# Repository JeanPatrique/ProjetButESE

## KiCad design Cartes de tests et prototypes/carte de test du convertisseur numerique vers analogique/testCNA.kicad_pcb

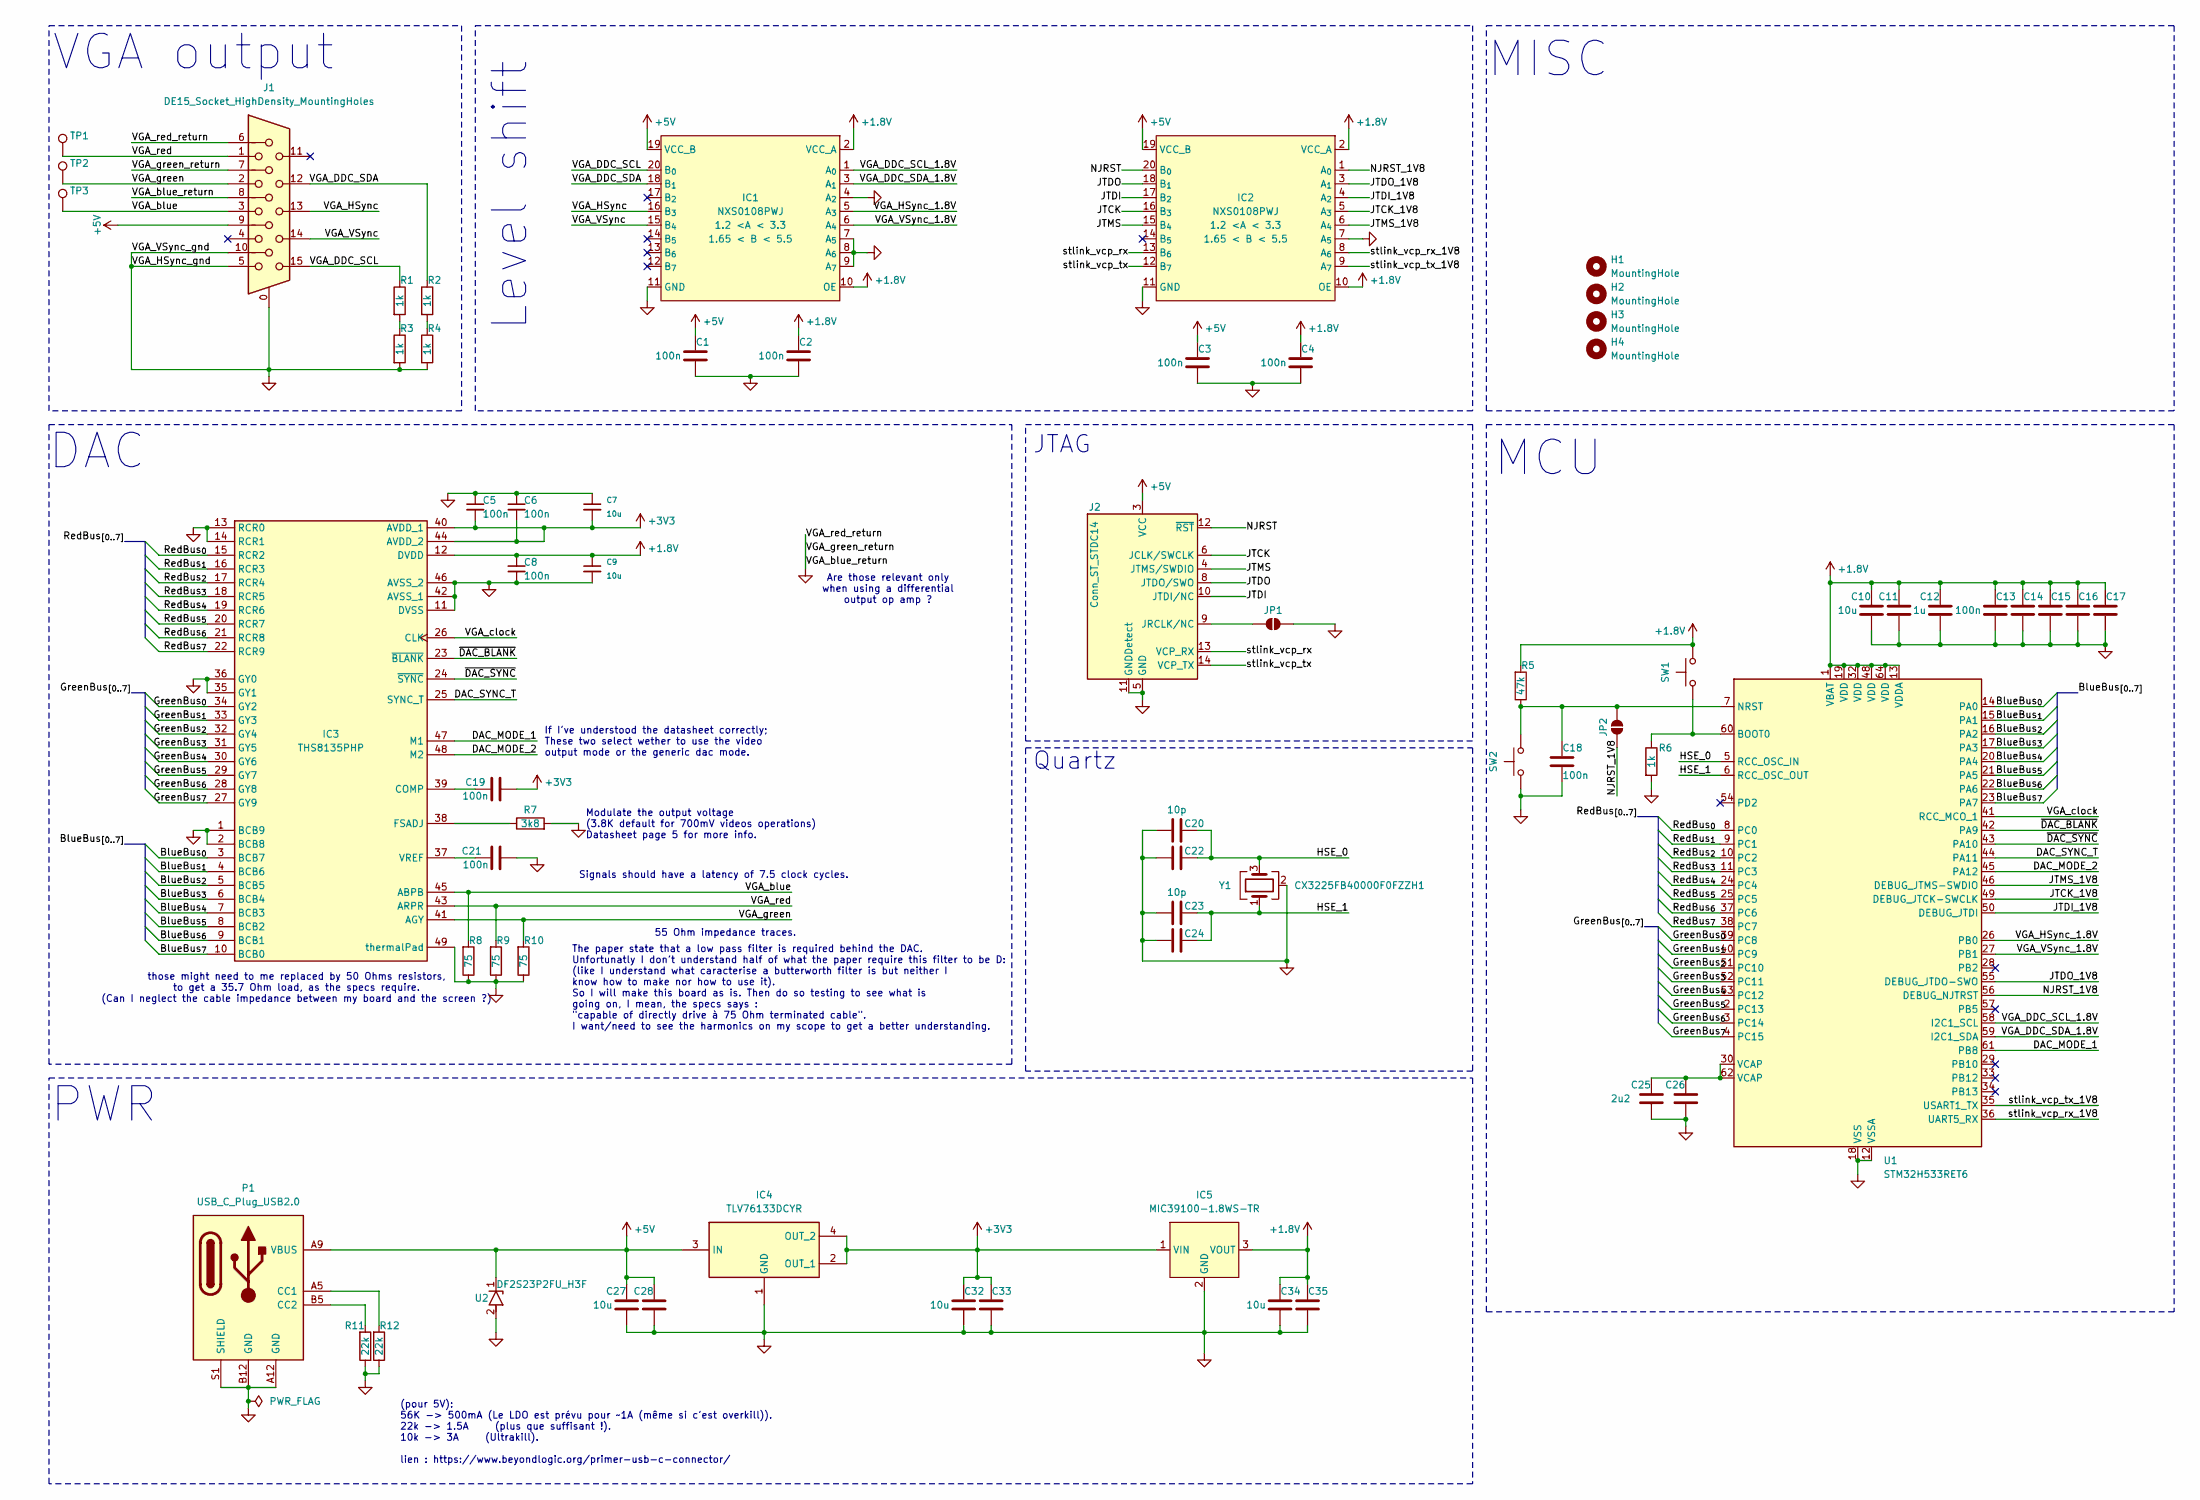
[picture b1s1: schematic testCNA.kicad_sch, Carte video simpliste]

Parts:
C1, C2, C3, C4, C5, C6, C8, C13, C14, C15, C16, C17, C18, C19, C21: 100n; C_0805_2012Metric_Pad1.18x1.45mm_HandSolder; Mouser Part Number 581-08055C104ZAT2A
C7, C9, C10, C11, C27, C28, C32, C33, C34, C35: 10u; C_1206_3216Metric_Pad1.33x1.80mm_HandSolder; Mouser Part Number 603-CC126ZKY5V7BB106
C12: 1u; C_1206_3216Metric_Pad1.33x1.80mm_HandSolder; Mouser Part Number 810-C3216X7R1H105K
C20, C22, C23, C24: 10p; C_1206_3216Metric_Pad1.33x1.80mm_HandSolder; Mouser Part Number 80-C1206C100J5GACTU
C25, C26: 2u2; C_1206_3216Metric_Pad1.33x1.80mm_HandSolder; Mouser Part Number 603-CC126KKX7R6BB225
H1, H2, H3, H4: MountingHole; MountingHole_3.2mm_M3
IC1, IC2: NXS0108PWJ; TSSOP-20_4.4x6.5mm_P0.65mm; Mouser Part Number 771-NXS0108PWJ
IC3: THS8135PHP; Texas_PHP0048E_HTQFP-48-1EP_7x7mm_P0.5mm_EP6.5x6.5mm_Mask3.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; Mouser Part Number 595-THS8135PHP
IC4: TLV76133DCYR; SOT-223; Mouser Part Number 595-TLV76133DCYR
IC5: MIC39100-1.8WS-TR; SOT-223-3_TabPin2; Mouser Part Number 998-MIC39100-1.8WSTR
J1: DE15_Socket_HighDensity_MountingHoles; DSUB-15_Socket_Horizontal_P2.77x2.84mm_EdgePinOffset7.70mm_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
J2: Conn_ST_STDC14; PinHeader_2x07_P1.27mm_Vertical_SMD
JP1, JP2: SolderJumper_2_Open; SolderJumper-2_P1.3mm_Open_RoundedPad1.0x1.5mm
P1: USB_C_Plug_USB2.0; USB_C_Receptacle_GCT_USB4125-xx-x-0190_6P_TopMnt_Horizontal; Mouser Part Number 179-UJCHGSMT2P6TR
R1, R2, R3, R4, R6: 1k; R_1206_3216Metric_Pad1.30x1.75mm_HandSolder; Mouser Part Number 603-RT1206DRD071KL
R5: 47k; R_1206_3216Metric_Pad1.30x1.75mm_HandSolder; Mouser Part Number 603-RT1206FRD0747KL
R7: 3k8; R_1206_3216Metric_Pad1.30x1.75mm_HandSolder; Mouser Part Number 603-RT1206BRD073K83L
R8, R9, R10: 75; R_1206_3216Metric_Pad1.30x1.75mm_HandSolder; Mouser Part Number 667-ERA-8AEB750V
R11, R12: 22k; R_1206_3216Metric_Pad1.30x1.75mm_HandSolder; Mouser Part Number 603-RT1206FRD0722KL
SW1, SW2: TS02-66-100-BK-100-SCR-D; SW_PUSH_6mm_H4.3mm; Mouser Part Number 179-TS0266100BK100SC
TP1, TP2, TP3: TestPoint; TestPoint_THTPad_D2.0mm_Drill1.0mm
U1: STM32H533RET6; LQFP-64_10x10mm_P0.5mm; Mouser Part Number 511-STM32H533RET6
U2: DF2S23P2FU_H3F; D_SOD-323_HandSoldering; Mouser Part Number 757-DF2S23P2FUH3F
Y1: CX3225FB40000F0FZZH1; Crystal_SMD_3225-4Pin_3.2x2.5mm_HandSoldering; Mouser Part Number 581-CX3225FB40F0FZZH

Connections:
+1.8V: C2.1, C4.1, C8.1, C9.1, C10.1, C11.1, C12.1, C13.1, C14.1, C15.1, C16.1, C17.1, C34.1, C35.1, IC1.2 (VCC_A), IC1.10 (OE), IC2.2 (VCC_A), IC2.10 (OE), IC3.12 (DVDD), IC5.3 (VOUT), R5.1, SW1.2, U1.1 (VBAT), U1.13 (VDDA), U1.19 (VDD), U1.32 (VDD), U1.48 (VDD), U1.64 (VDD)
+3V3: C5.2, C6.2, C7.2, C19.2, C32.1, C33.1, IC3.40 (AVDD_1), IC3.44 (AVDD_2), IC4.2 (OUT_1), IC4.4 (OUT_2), IC5.1 (VIN)
+5V: C1.1, C3.1, C27.1, C28.1, IC1.19 (VCC_B), IC2.19 (VCC_B), IC4.3 (IN), J1.9, J2.3 (VCC), P1.A9 (VBUS), P1.B9 (VBUS), U2.1
/BlueBus_{0}: IC3.3 (BCB7), U1.14 (PA0)
/BlueBus_{1}: IC3.4 (BCB6), U1.15 (PA1)
/BlueBus_{2}: IC3.5 (BCB5), U1.16 (PA2)
/BlueBus_{3}: IC3.6 (BCB4), U1.17 (PA3)
/BlueBus_{4}: IC3.7 (BCB3), U1.20 (PA4)
/BlueBus_{5}: IC3.8 (BCB2), U1.21 (PA5)
/BlueBus_{6}: IC3.9 (BCB1), U1.22 (PA6)
/BlueBus_{7}: IC3.10 (BCB0), U1.23 (PA7)
/DAC_MODE_1: IC3.47 (M1), U1.61 (PB8)
/DAC_MODE_2: IC3.48 (M2), U1.45 (PA12)
/DAC_SYNC_T: IC3.25 (SYNC_T), U1.44 (PA11)
/GreenBus_{0}: IC3.34 (GY2), U1.39 (PC8)
/GreenBus_{1}: IC3.33 (GY3), U1.40 (PC9)
/GreenBus_{2}: IC3.32 (GY4), U1.51 (PC10)
/GreenBus_{3}: IC3.31 (GY5), U1.52 (PC11)
/GreenBus_{4}: IC3.30 (GY6), U1.53 (PC12)
/GreenBus_{5}: IC3.29 (GY7), U1.2 (PC13)
/GreenBus_{6}: IC3.28 (GY8), U1.3 (PC14)
/GreenBus_{7}: IC3.27 (GY9), U1.4 (PC15)
/HSE_0: C20.2, C22.2, U1.5 (RCC_OSC_IN), Y1.3
/HSE_1: C23.2, C24.2, U1.6 (RCC_OSC_OUT), Y1.1
/JTCK: IC2.16 (B_{3}), J2.6 (JCLK/SWCLK)
/JTCK_1V8: IC2.5 (A_{3}), U1.49 (DEBUG_JTCK-SWCLK)
/JTDI: IC2.17 (B_{2}), J2.10 (JTDI/NC)
/JTDI_1V8: IC2.4 (A_{2}), U1.50 (DEBUG_JTDI)
/JTDO: IC2.18 (B_{1}), J2.8 (JTDO/SWO)
/JTDO_1V8: IC2.3 (A_{1}), U1.55 (DEBUG_JTDO-SWO)
/JTMS: IC2.15 (B_{4}), J2.4 (JTMS/SWDIO)
/JTMS_1V8: IC2.6 (A_{4}), U1.46 (DEBUG_JTMS-SWDIO)
/NJRST: IC2.20 (B_{0}), J2.12 (~RST)
/NJRST_1V8: IC2.1 (A_{0}), JP2.1 (A), U1.56 (DEBUG_NJTRST)
/RedBus_{0}: IC3.15 (RCR2), U1.8 (PC0)
/RedBus_{1}: IC3.16 (RCR3), U1.9 (PC1)
/RedBus_{2}: IC3.17 (RCR4), U1.10 (PC2)
/RedBus_{3}: IC3.18 (RCR5), U1.11 (PC3)
/RedBus_{4}: IC3.19 (RCR6), U1.24 (PC4)
/RedBus_{5}: IC3.20 (RCR7), U1.25 (PC5)
/RedBus_{6}: IC3.21 (RCR8), U1.37 (PC6)
/RedBus_{7}: IC3.22 (RCR9), U1.38 (PC7)
/VGA_DDC_SCL: IC1.20 (B_{0}), J1.15, R1.1
/VGA_DDC_SCL_1.8V: IC1.1 (A_{0}), U1.58 (I2C1_SCL)
/VGA_DDC_SDA: IC1.18 (B_{1}), J1.12, R2.1
/VGA_DDC_SDA_1.8V: IC1.3 (A_{1}), U1.59 (I2C1_SDA)
/VGA_HSync: IC1.16 (B_{3}), J1.13
/VGA_HSync_1.8V: IC1.5 (A_{3}), U1.26 (PB0)
/VGA_VSync: IC1.15 (B_{4}), J1.14
/VGA_VSync_1.8V: IC1.6 (A_{4}), U1.27 (PB1)
/VGA_blue: IC3.45 (ABPB), J1.3, R8.1, TP3.1
/VGA_clock: IC3.26 (CLK), U1.41 (RCC_MCO_1)
/VGA_green: IC3.41 (AGY), J1.2, R10.1, TP2.1
/VGA_red: IC3.43 (ARPR), J1.1, R9.1, TP1.1
/stlink_vcp_rx: IC2.13 (B_{6}), J2.13 (VCP_RX)
/stlink_vcp_rx_1V8: IC2.8 (A_{6}), U1.36 (UART5_RX)
/stlink_vcp_tx: IC2.12 (B_{7}), J2.14 (VCP_TX)
/stlink_vcp_tx_1V8: IC2.9 (A_{7}), U1.35 (USART1_TX)
/~DAC_BLANK: IC3.23 (~BLANK), U1.42 (PA9)
/~DAC_SYNC: IC3.24 (~SYNC), U1.43 (PA10)
GND: C1.2, C2.2, C3.2, C4.2, C5.1, C6.1, C7.1, C8.2, C9.2, C10.2, C11.2, C12.2, C13.2, C14.2, C15.2, C16.2, C17.2, C18.2, C20.1, C21.2, C22.1, C23.1, C24.1, C25.2, C26.2, C27.2, C28.2, C32.2, C33.2, C34.2, C35.2, IC1.4 (A_{2}), IC1.7 (A_{5}), IC1.8 (A_{6}), IC1.9 (A_{7}), IC1.11 (GND), IC2.7 (A_{5}), IC2.11 (GND), IC3.1 (BCB9), IC3.2 (BCB8), IC3.11 (DVSS), IC3.13 (RCR0), IC3.14 (RCR1), IC3.35 (GY1), IC3.36 (GY0), IC3.42 (AVSS_1), IC3.46 (AVSS_2), IC3.49 (thermalPad), IC4.1 (GND), IC5.2 (GND), J1.0, J1.5, J1.6, J1.7, J1.8, J1.10, J2.5 (GND), J2.7 (GND), J2.11 (GNDDetect), JP1.2 (B), P1.A12 (GND), P1.B12 (GND), P1.S1 (SHIELD), R3.2, R4.2, R6.2, R7.2, R8.2, R9.2, R10.2, R11.2, R12.2, SW2.1, U1.12 (VSSA), U1.18 (VSS), U1.31 (VSS), U1.47 (VSS), U1.63 (VSS), U2.2, Y1.2 (G), Y1.4 (G)
unnamed: C25.1, C26.1, U1.30 (VCAP), U1.62 (VCAP)
unnamed: C19.1, IC3.39 (COMP)
unnamed: IC3.38 (FSADJ), R7.1
unnamed: C21.1, IC3.37 (VREF)
unnamed: J2.9 (JRCLK/NC), JP1.1 (A)
unnamed: C18.1, JP2.2 (B), R5.2, SW2.2, U1.7 (NRST)
unnamed: P1.A5 (CC1), R12.1
unnamed: P1.B5 (CC2), R11.1
unnamed: R1.2, R3.1
unnamed: R2.2, R4.1
unnamed: R6.1, SW1.1, U1.60 (BOOT0)

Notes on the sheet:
The paper state that a low pass filter is required behind the DAC. Unfortunatly I don't understand half of what the paper require this filter to be D: (like I understand what caracterise a butterworth filter is but neither I know how to make nor how to use it). So I will make this board as is. Then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
(pour 5V): 56K -> 500mA (Le LDO est prévu pour ~1A (même si c'est overkill)). 22k -> 1.5A (plus que suffisant !). 10k -> 3A (Ultrakill). lien : https://www.beyondlogic.org/primer-usb-c-connector/
If I've understood the datasheet correctly; These two select wether to use the video output mode or the generic dac mode.
MCU
VGA output
PWR
JTAG
those might need to me replaced by 50 Ohms resistors, to get a 35.7 Ohm load, as the specs require. (Can I neglect the cable impedance between my board and the screen ?)
Are those relevant only when using a differential output op amp ?
Quartz
Modulate the output voltage (3.8K default for 700mV videos operations) Datasheet page 5 for more info.
MISC
Level shift
DAC
55 Ohm impedance traces.
Signals should have a latency of 7.5 clock cycles.

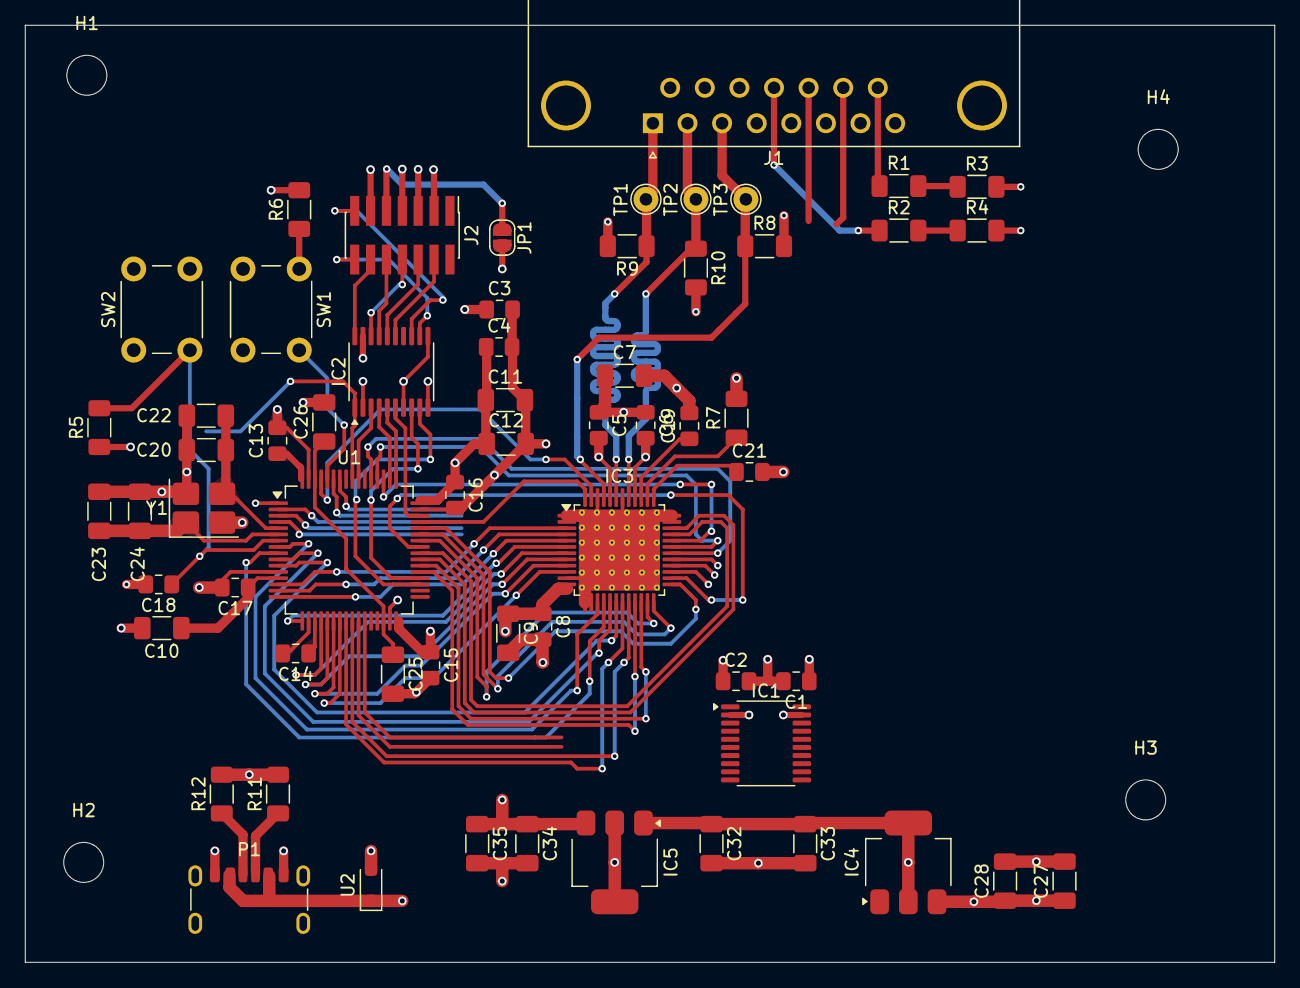
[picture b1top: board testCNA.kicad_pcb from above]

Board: 4 copper layers, 100.0 x 75.0 mm, 66 parts (1 on the bottom side), 72 nets.

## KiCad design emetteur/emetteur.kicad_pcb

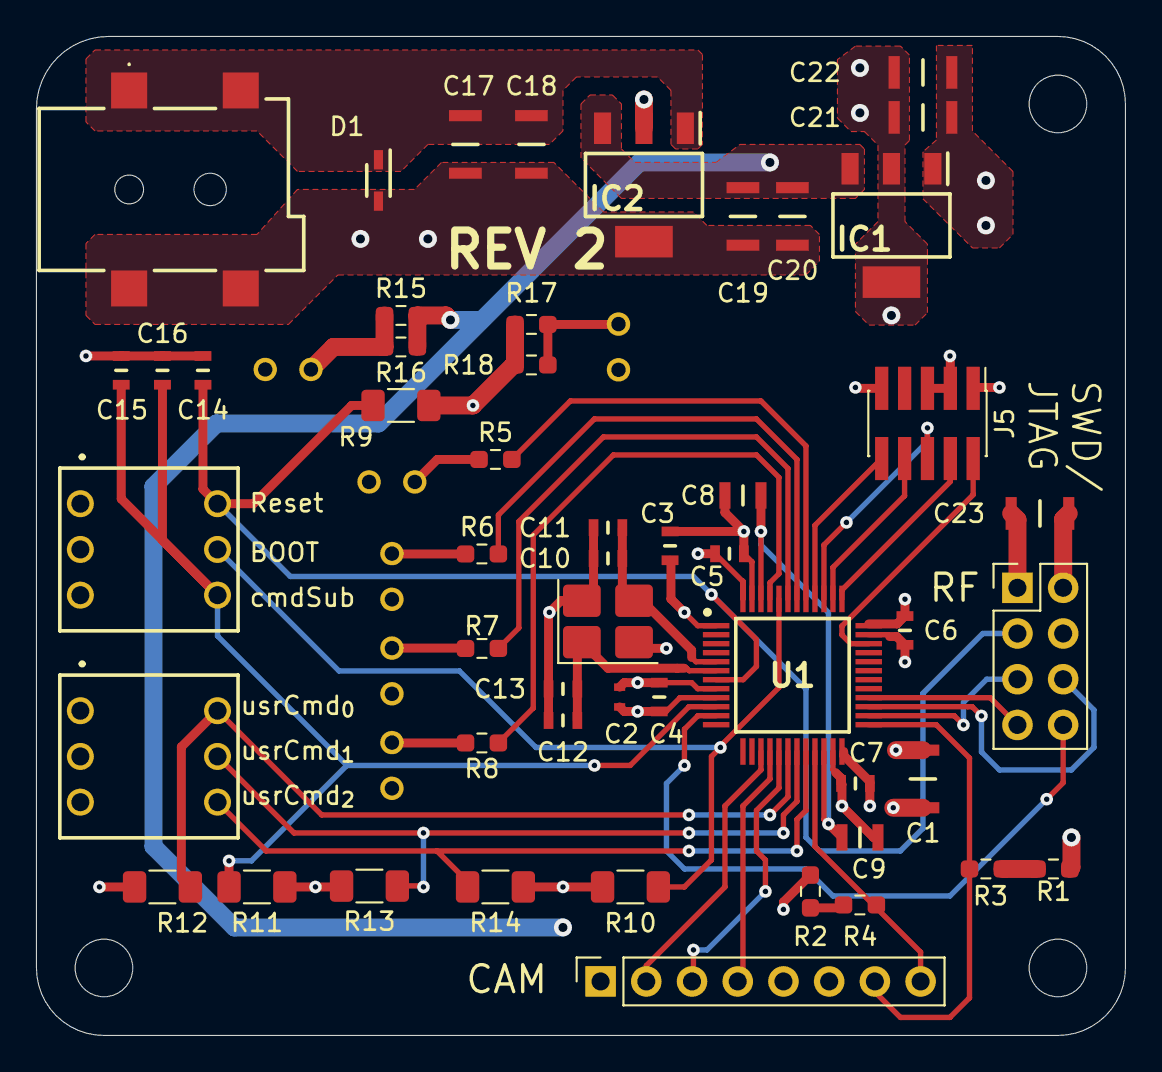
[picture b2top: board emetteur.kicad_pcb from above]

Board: 4 copper layers, 60.5 x 55.5 mm, 61 parts (0 on the bottom side), 39 nets.

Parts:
C1, C17, C18, C19, C20, C21, C22, C23: 47u; C_47u_CAPC3216X180N
C2: 1u; C_1u_CAPC1005X55N
C3, C4, C5, C6, C7, C14, C15, C16: 100n; C_100n_CAPC1608X80N
C8, C9: 2u2; C_2u2_CAPC2012X145N
C10, C11, C12, C13: 10p; C_10p_CAPC1608X80N
D1: DF2S23P2FU,H3F; Diode_TVS_SOD2513X115N
H1, H2, H3: MountingHole; MountingHole_3.2mm_M3
IC1: regulateur_3V3_1A_TLV76133DCYR; regulateur_3V3_1A_SOT230P700X180-4N
IC2: LM7805MPX_NOPB; regulateur_5V_SOT230P700X180-4N
J1: PJ-114AH-SMT-TR; PowerJackCon_PJ114AHSMTTR
J3: Conn_02x04_Odd_Even; PinSocket_2x04_P2.54mm_Vertical_fliped
J4: Conn_01x08_Pin; PinSocket_1x08_P2.54mm_Vertical
J5: Conn_ARM_JTAG_SWD_10; PinHeader_2x05_P1.27mm_Vertical_SMD
LED1: Rouge; led_verte_T-1_3MM_
LED2, LED3, LED4, LED5, LED6: Verte; led_verte_T-1_3MM_
R1, R2, R3, R4, R15, R16, R17, R18: 1k; R_0603_1608Metric_Pad0.98x0.95mm_HandSolder
R5, R6, R7, R8: 82; R_0603_1608Metric_Pad0.98x0.95mm_HandSolder
R9, R10, R11, R12, R13, R14: 10K; R_1206_3216Metric_Pad1.30x1.75mm_HandSolder
S1, S2: DS01C-254-L-03BE; switch_3_DS01C254L03BE
U1: STM32H523CET6; MCU_QFP50P900X900X160-48N
Y1: CX3225FB40000F0FZZH1; Crystal_SMD_3225-4Pin_3.2x2.5mm_HandSoldering

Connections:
+3.3V: C1.1, C2.2, C3.1, C4.1, C5.1, C6.1, C7.1, C21.1, C22.1, C23.1, IC1.2 (OUT_1), IC1.4 (OUT_2), J3.2 (VCC), J4.1, J5.1 (VTref), R1.1, R2.1, R9.1, R17.1, R18.1, S1.3 (COM_{1}), S1.5 (COM_{2}), S2.1 (COM_{0}), S2.3 (COM_{1}), S2.5 (COM_{2}), U1.1 (VBAT), U1.9 (VDDA), U1.24 (VDD_1), U1.36 (VDD_2), U1.48 (VDD_3)
+5V: C19.1, C20.1, IC1.3 (IN), IC2.3 (OUTPUT), J4.5, R15.1, R16.1
+9/28V: C17.1, C18.1, D1.1 (K), IC2.1 (INPUT), J1.+
/Émetteur caméra/BootMode: R10.2, S1.4 (NO_{1}), U1.44 (BOOT0)
/Émetteur caméra/HSE_0: C10.1, C11.1, U1.5 (OSC_IN), Y1.3
/Émetteur caméra/HSE_1: C12.1, C13.1, U1.6 (OSC_OUT), Y1.1
/Émetteur caméra/I2C_{2}_SCL: J4.8, R4.2, U1.21 (PB10)
/Émetteur caméra/I2C_{2}_SDA: J4.7, R3.2, U1.25 (PB12)
/Émetteur caméra/IRQ_{0}: J3.8 (IRQ), U1.11 (PA1)
/Émetteur caméra/JTCK/SWCLK: J5.4 (SWCLK/TCK), U1.37 (PA14)
/Émetteur caméra/JTDI: J5.8 (NC/TDI), U1.38 (PA15)
/Émetteur caméra/JTDO: J5.6 (SWO/TDO), U1.39 (PB3)
/Émetteur caméra/JTMS/SWDIO: J5.2 (SWDIO/TMS), U1.34 (PA13)
/Émetteur caméra/JTNRST: J5.10 (~RESET), U1.40 (PB4)
/Émetteur caméra/SPI_{1}_MISO: J4.4, U1.16 (PA6)
/Émetteur caméra/SPI_{1}_MOSI: J4.3, U1.17 (PA7)
/Émetteur caméra/SPI_{1}_SCLK: J4.2, U1.15 (PA5)
/Émetteur caméra/SPI_{2}_MISO: J3.6 (MOSI), U1.27 (PB14)
/Émetteur caméra/SPI_{2}_MOSI: J3.7 (MISO), U1.28 (PB15)
/Émetteur caméra/SPI_{2}_SCLK: J3.5 (SCL), U1.26 (PB13)
/Émetteur caméra/dbgUsrLed_{0}: R5.1, U1.41 (PB5)
/Émetteur caméra/dbgUsrLed_{1}: R6.1, U1.42 (PB6)
/Émetteur caméra/dbgUsrLed_{2}: R7.1, U1.43 (PB7)
/Émetteur caméra/dbgUsrLed_{3}: R8.1, U1.45 (PB8)
/Émetteur caméra/usrCmd_{0}: R12.2, S2.2 (NO_{0}), U1.18 (PB0)
/Émetteur caméra/usrCmd_{1}: R13.2, S2.4 (NO_{1}), U1.19 (PB1)
/Émetteur caméra/usrCmd_{2}: R14.2, S2.6 (NO_{2}), U1.20 (PB2)
/Émetteur caméra/usrSubmitCmd: C15.1, C16.1, R11.2, S1.6 (NO_{2}), U1.10 (PA0)
/Émetteur caméra/~RESET: C14.1, J3.3 (CE), R9.2, S1.2 (NO_{0}), U1.7 (~RESET)
GND: C1.2, C2.1, C3.2, C4.2, C5.2, C6.2, C7.2, C8.1, C9.1, C10.2, C11.2, C12.2, C13.2, C14.2, C15.2, C16.2, C17.2, C18.2, C19.2, C20.2, C21.2, C22.2, C23.2, D1.2 (A), IC1.1 (GND), IC2.2 (GND_{1}), IC2.4 (GND_{2}), J1.-, J3.1 (GND), J3.4 (~CS), J4.6, J5.3 (GND), J5.5 (GND), J5.9 (GNDDetect), LED1.1 (K), LED2.1 (K), LED3.1 (K), LED4.1 (K), LED5.1 (K), LED6.1 (K), R10.1, R11.1, R12.1, R13.1, R14.1, S1.1 (COM_{0}), U1.8 (VSSA), U1.23 (VSS_1), U1.35 (VSS_2), U1.47 (VSS_3), Y1.2, Y1.4
unnamed: LED1.2 (A), R5.2
unnamed: LED2.2 (A), R6.2
unnamed: LED3.2 (A), R7.2
unnamed: LED4.2 (A), R8.2
unnamed: LED5.2 (A), R15.2, R16.2
unnamed: LED6.2 (A), R17.2, R18.2
unnamed: R1.2, R3.1
unnamed: R2.2, R4.1
unnamed: C8.2, C9.2, U1.22 (VCAP_1), U1.46 (VCAP_2)
